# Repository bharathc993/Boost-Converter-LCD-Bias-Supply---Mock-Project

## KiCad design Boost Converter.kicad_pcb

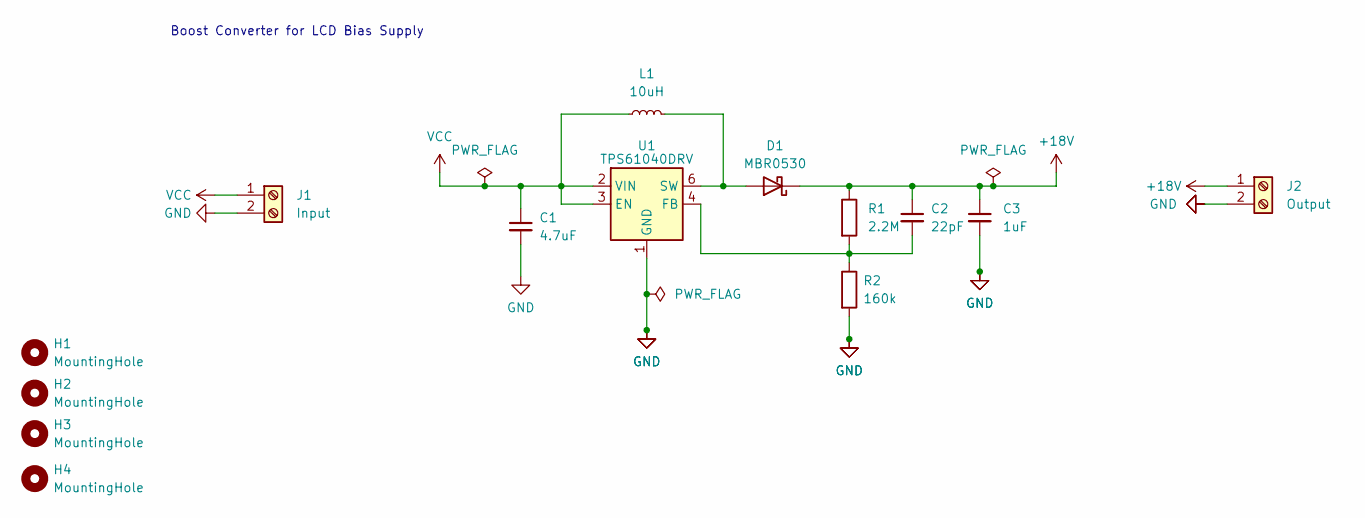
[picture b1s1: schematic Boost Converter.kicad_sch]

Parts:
C1: 4.7uF; CP_Radial_D4.0mm_P1.50mm
C2: 22pF; C_0603_1608Metric
C3: 1uF; C_0603_1608Metric
D1: MBR0530; D_SOD-123
H1, H2, H3, H4: MountingHole; MountingHole_2.1mm
J1: Input; TerminalBlock_Phoenix_MPT-0,5-2-2.54_1x02_P2.54mm_Horizontal
J2: Output; TerminalBlock_Phoenix_MPT-0,5-2-2.54_1x02_P2.54mm_Horizontal
L1: 10uH; L_Wurth_WE-LQSH-3012
R1: 2.2M; R_0805_2012Metric
R2: 160k; R_0603_1608Metric
U1: TPS61040DRV; WSON-6-1EP_2x2mm_P0.65mm_EP1x1.6mm

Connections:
+18V: C2.1, C3.1, D1.1 (K), J2.1, R1.1
GND: C1.2, C3.2, J1.2, J2.2, R2.2, U1.1 (GND)
unnamed: D1.2 (A), L1.2, U1.6 (SW)
unnamed: C2.2, R1.2, R2.1, U1.4 (FB)
VCC: C1.1, J1.1, L1.1, U1.2 (VIN), U1.3 (EN)

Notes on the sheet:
Boost Converter for LCD Bias Supply

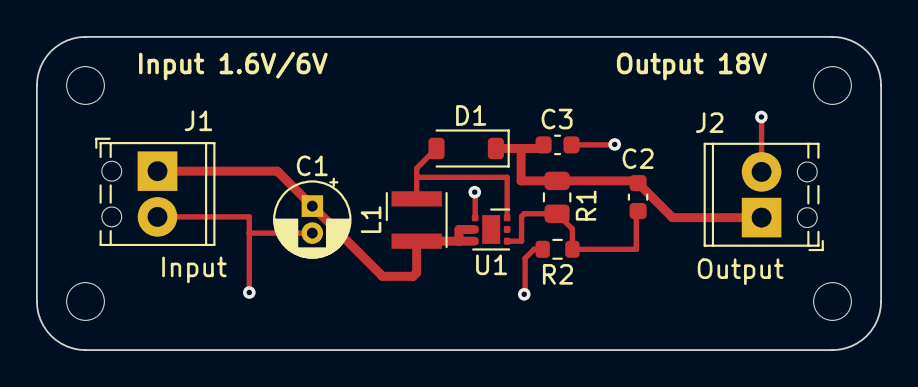
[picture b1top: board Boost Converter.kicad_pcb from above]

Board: 2 copper layers, 46.9 x 17.4 mm, 14 parts (0 on the bottom side), 5 nets.
